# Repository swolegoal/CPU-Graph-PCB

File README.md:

# Arduino-based CPU Graph PCB

## Opening this project

Launch KiCAD and `Open` the `CPU_meter.pro` file.

## Disclaimer

This is my first PCB ever!  I designed it using KiCAD on my Arch Linux laptop.

## What's done (*for now*)

- Schematic diagram
- Select and make footprints

## TODO

- Finalize board layout

## LICENSE

The project is licensed under the terms of the GPLv2 license.  See the included `LICENSE` file for more information.

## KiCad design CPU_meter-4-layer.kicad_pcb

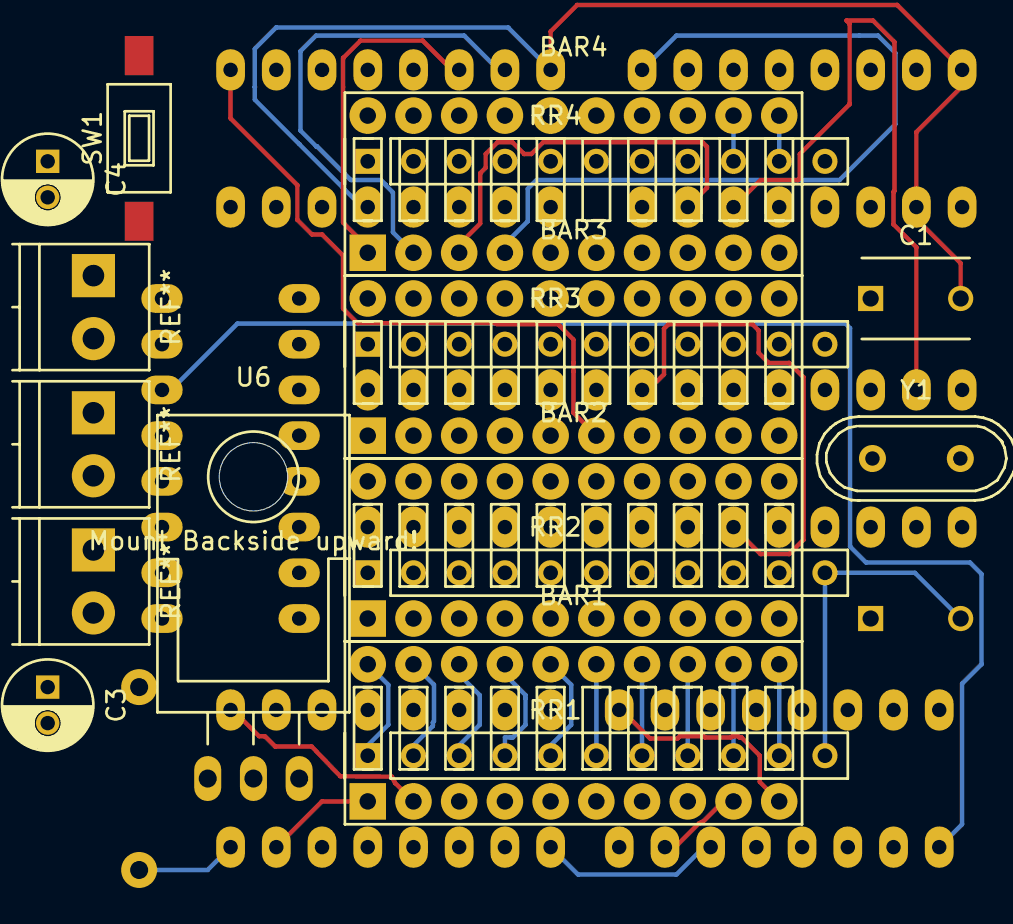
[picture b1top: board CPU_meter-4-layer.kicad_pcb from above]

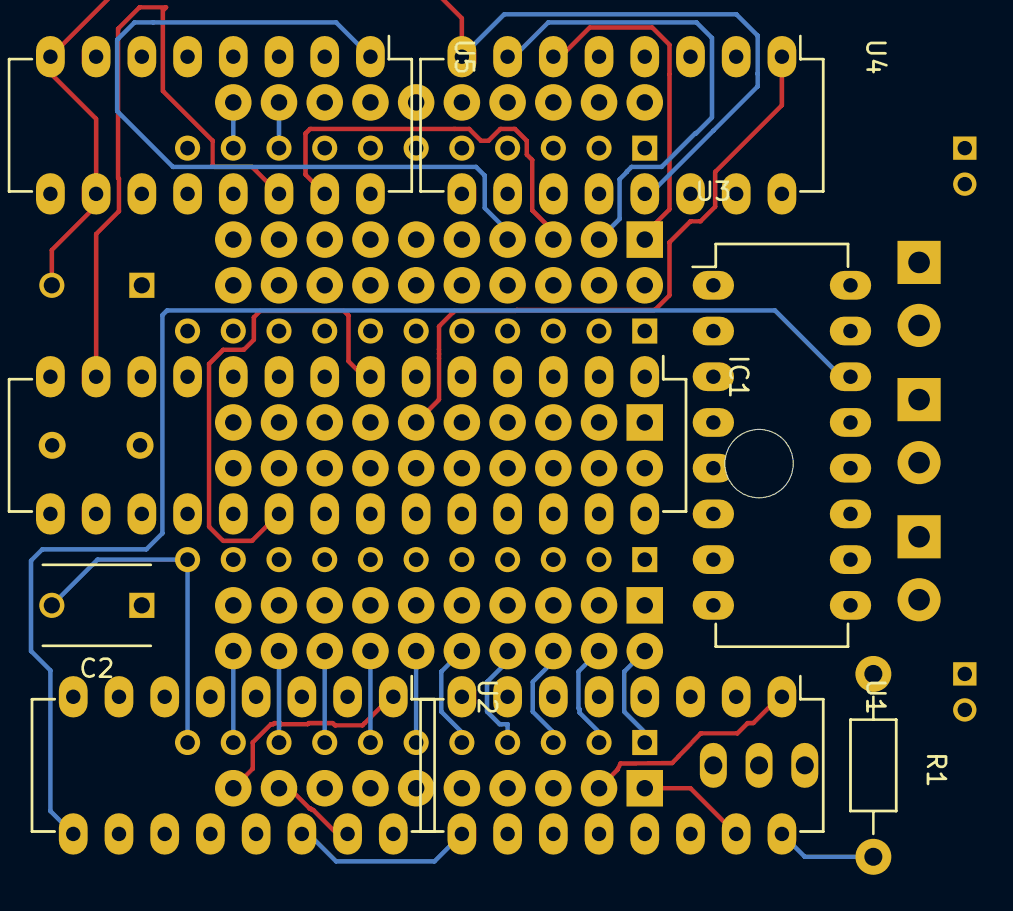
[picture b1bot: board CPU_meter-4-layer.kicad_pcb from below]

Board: 4 copper layers, 22 parts (8 on the bottom side), 93 nets.

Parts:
BAR1, BAR2, BAR3, BAR4: DOT-BAR2; HDSP-48xx
C1, C2: 22 pF; C_Disc_D6_P5
C3, C4: 100 uF; C_Radial_D5_L11_P2
IC1: ATMEGA328P-P; DIP-28_W7.62mm_LongPads
R1: 10K; Resistor_Horizontal_RM10mm
RR1, RR2, RR3, RR4: RR8; Resistor_Array_SIP10
SW1: SPST; SW_SPST_FSMSM
U1, U2, U3, U4, U5: 74HC595; DIP-16_W7.62mm_LongPads
U6: LM7805; TO-220_Neutral123_Horizontal_Reverse
Y1: 16.00 MHz; Crystal_HC49-U_Vertical

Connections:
GND: C1.2, C2.2, C3.2, C4.2, IC1.8, IC1.22, RR1.11, RR2.11, RR3.11, RR4.11, SW1.2, U1.8, U1.10, U1.13, U2.8, U2.10, U2.13, U3.8, U3.10, U3.13, U4.8, U4.10, U4.13, U5.8, U5.10, U5.13
unnamed: BAR1.1, U1.15
unnamed: BAR1.2, U1.1
unnamed: BAR1.3, U1.2
unnamed: BAR1.4, U1.3
unnamed: BAR1.5, U1.4
unnamed: BAR1.6, U1.5
unnamed: BAR1.7, U1.6
unnamed: BAR1.8, U1.7
unnamed: BAR1.9, U2.15
unnamed: BAR1.10, U2.1
unnamed: BAR1.11, RR1.10
unnamed: BAR1.12, RR1.9
unnamed: BAR1.13, RR1.8
unnamed: BAR1.14, RR1.7
unnamed: BAR1.15, RR1.6
unnamed: BAR1.16, RR1.5
unnamed: BAR1.17, RR1.4
unnamed: BAR1.18, RR1.3
unnamed: BAR1.19, RR1.2
unnamed: BAR1.20, RR1.1
unnamed: BAR2.1, U2.2
unnamed: BAR2.2, U2.3
unnamed: BAR2.3, U2.4
unnamed: BAR2.4, U2.5
unnamed: BAR2.5, U2.6
unnamed: BAR2.6, U2.7
unnamed: BAR2.7, U3.15
unnamed: BAR2.8, U3.1
unnamed: BAR2.9, U3.2
unnamed: BAR2.10, U3.3
unnamed: BAR2.11, RR2.10
unnamed: BAR2.12, RR2.9
unnamed: BAR2.13, RR2.8
unnamed: BAR2.14, RR2.7
unnamed: BAR2.15, RR2.6
unnamed: BAR2.16, RR2.5
unnamed: BAR2.17, RR2.4
unnamed: BAR2.18, RR2.3
unnamed: BAR2.19, RR2.2
unnamed: BAR2.20, RR2.1
unnamed: BAR3.1, U3.4
unnamed: BAR3.2, U3.5
unnamed: BAR3.3, U3.6
unnamed: BAR3.4, U3.7
unnamed: BAR3.5, U4.15
unnamed: BAR3.6, U4.1
unnamed: BAR3.7, U4.2
unnamed: BAR3.8, U4.3
unnamed: BAR3.9, U4.4
unnamed: BAR3.10, U4.5
unnamed: BAR3.11, RR3.10
unnamed: BAR3.12, RR3.9
unnamed: BAR3.13, RR3.8
unnamed: BAR3.14, RR3.7
unnamed: BAR3.15, RR3.6
unnamed: BAR3.16, RR3.5
unnamed: BAR3.17, RR3.4
unnamed: BAR3.18, RR3.3
unnamed: BAR3.19, RR3.2
unnamed: BAR3.20, RR3.1
unnamed: BAR4.1, U4.6
unnamed: BAR4.2, U4.7
unnamed: BAR4.3, U5.15
unnamed: BAR4.4, U5.1
unnamed: BAR4.5, U5.2
unnamed: BAR4.6, U5.3
unnamed: BAR4.7, U5.4
unnamed: BAR4.8, U5.5
unnamed: BAR4.9, U5.6
unnamed: BAR4.10, U5.7
unnamed: BAR4.11, RR4.10
unnamed: BAR4.12, RR4.9
unnamed: BAR4.13, RR4.8
unnamed: BAR4.14, RR4.7
unnamed: BAR4.15, RR4.6
unnamed: BAR4.16, RR4.5
unnamed: BAR4.17, RR4.4
unnamed: BAR4.18, RR4.3
unnamed: BAR4.19, RR4.2
unnamed: BAR4.20, RR4.1
unnamed: C1.1, IC1.10, Y1.1
unnamed: C2.1, IC1.9, Y1.2
unnamed: IC1.1, R1.1, SW1.1
unnamed: IC1.13, U5.14
unnamed: IC1.14, U1.12
unnamed: IC1.16, U5.12
unnamed: IC1.17, U1.14, U2.12, U3.12, U4.12
unnamed: IC1.18, U1.11, U2.11, U3.11, U4.11, U5.11
unnamed: U1.9, U2.14
unnamed: U2.9, U3.14
unnamed: U3.9, U4.14
VCC: C4.1, IC1.7, IC1.20, R1.2, U1.16, U2.16, U3.16, U4.16, U5.16

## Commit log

2016-07-26 How to open
2016-08-02 Added cache library file, just in case :)
2016-08-02 Added rescue library file, just in case :)
2016-08-02 PCB progress :)
2016-08-02 Added image of schematic diagram :)
2016-08-03 Finalized the board layout for first prototype run!
